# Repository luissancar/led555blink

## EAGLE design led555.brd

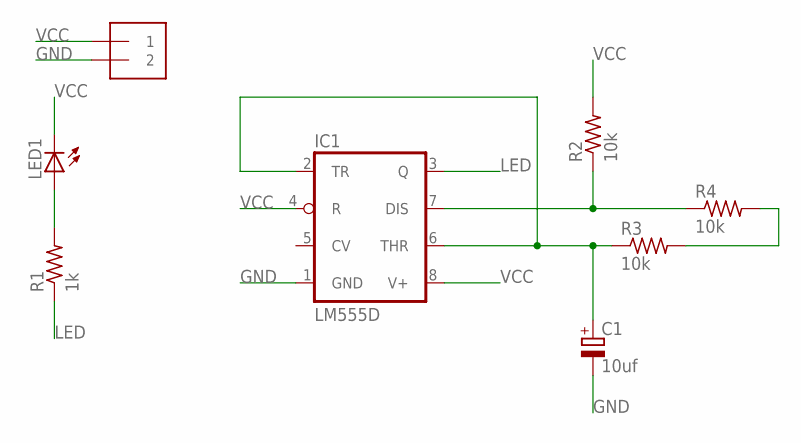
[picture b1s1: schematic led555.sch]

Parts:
C1: 10uf; 140CLH-0810
IC1: LM555D; SO08
J1: power; 1X2-3.5MM
LED1: LED5MM
R1: 1k; M1206
R2, R3, R4: 10k; M1206

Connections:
GND: C1.-, IC1.1 (GND), J1.2
LED: IC1.3 (Q), R1.1
unnamed: LED1.A, R1.2
unnamed: C1.+, IC1.2 (TR), IC1.6 (THR), R3.1
unnamed: R3.2, R4.2
unnamed: IC1.7 (DIS), R2.1, R4.1
VCC: IC1.4 (R), IC1.8 (V+), J1.1, LED1.K (C), R2.2

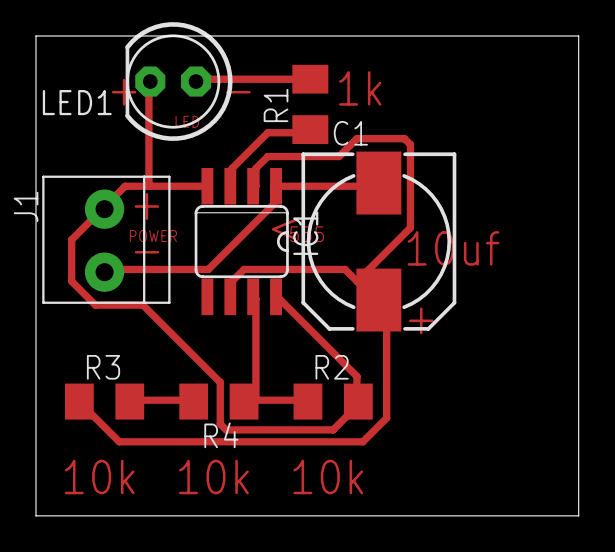
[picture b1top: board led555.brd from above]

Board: 2 copper layers, 30.1 x 26.7 mm, 8 parts (0 on the bottom side), 7 nets.
